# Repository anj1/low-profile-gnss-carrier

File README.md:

KiCAD schematic and pcb for a low profile GNSS module carrier (<3 mm thickness) using ublox MAX-M10S module and interfacing to 1.8V UART. This is for a project for adding gnss to a Kobo Clara Colour.

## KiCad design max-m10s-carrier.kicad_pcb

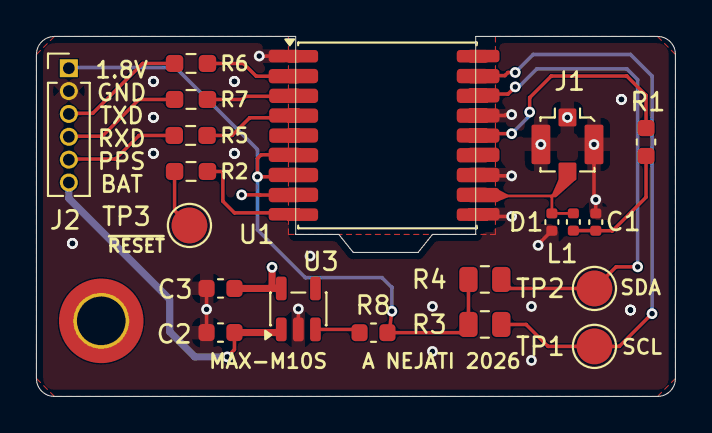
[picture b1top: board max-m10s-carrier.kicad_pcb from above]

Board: 4 copper layers, 35.5 x 20.0 mm, 21 parts (0 on the bottom side), 18 nets.

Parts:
 : MountingHole_2.7mm_M2.5_DIN965_Pad_TopBottom
C1: 47p; C_0402_1005Metric
C2, C3: 1u; C_0603_1608Metric
D1: PESD0402-0402T; C_0402_1005Metric
J1: U.FL; U.FL_Molex_MCRF_73412-0110_Vertical
J2: Conn_01x06_Pin; PinHeader_1x06_P1.27mm_Vertical
L1: RFC; C_0402_1005Metric
R1: 10; C_0603_1608Metric
R2, R5, R6, R7: 33; R_0603_1608Metric_Pad0.98x0.95mm_HandSolder
R3, R4: 2.2k; R_0805_2012Metric
R8: 1k; C_0603_1608Metric
TP1: SCL; TestPoint_Pad_D2.0mm
TP2: SDA; TestPoint_Pad_D2.0mm
TP3: ~{RESET}; TestPoint_Pad_D2.0mm
U1: MAX-M10S; ublox_MAX
U3: MIC5317-3.3xM5; SOT-23-5

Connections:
+1V8: J2.1, R3.2, R4.2, R8.1, U1.6 (V_BCKP), U1.7 (VCC_IO)
+3V3: C3.1, U1.8 (VCC), U3.5 (VOUT)
+BATT: C2.1, J2.6, U3.1 (VIN)
/PPS: J2.5, R5.2
/RXD: J2.4, R7.1
/TXD: J2.3, R6.1
/~RESET: R2.1, TP3.1 (1_1)
GND: C1.2, C2.2, C3.2, D1.1 (A1), J1.2 (Ext), J2.2, U1.1 (GND), U1.10 (GND), U1.12 (GND), U1.15 (VIO_SEL), U3.2 (GND)
unnamed: C1.1, L1.1, R1.2
unnamed: D1.2 (A2), J1.1 (In), L1.2, U1.11 (RF_IN)
unnamed: R7.2, U1.3 (RXD)
unnamed: R3.1, TP1.1 (1_1), U1.17 (SCL)
unnamed: R4.1, TP2.1 (1_1), U1.16 (SDA)
unnamed: R5.1, U1.4 (TIMEPULSE)
unnamed: R6.2, U1.2 (TXD)
unnamed: R1.1, U1.14 (VCC_RF)
unnamed: R2.2, U1.9 (~RESET)
unnamed: R8.2, U3.3 (EN)
